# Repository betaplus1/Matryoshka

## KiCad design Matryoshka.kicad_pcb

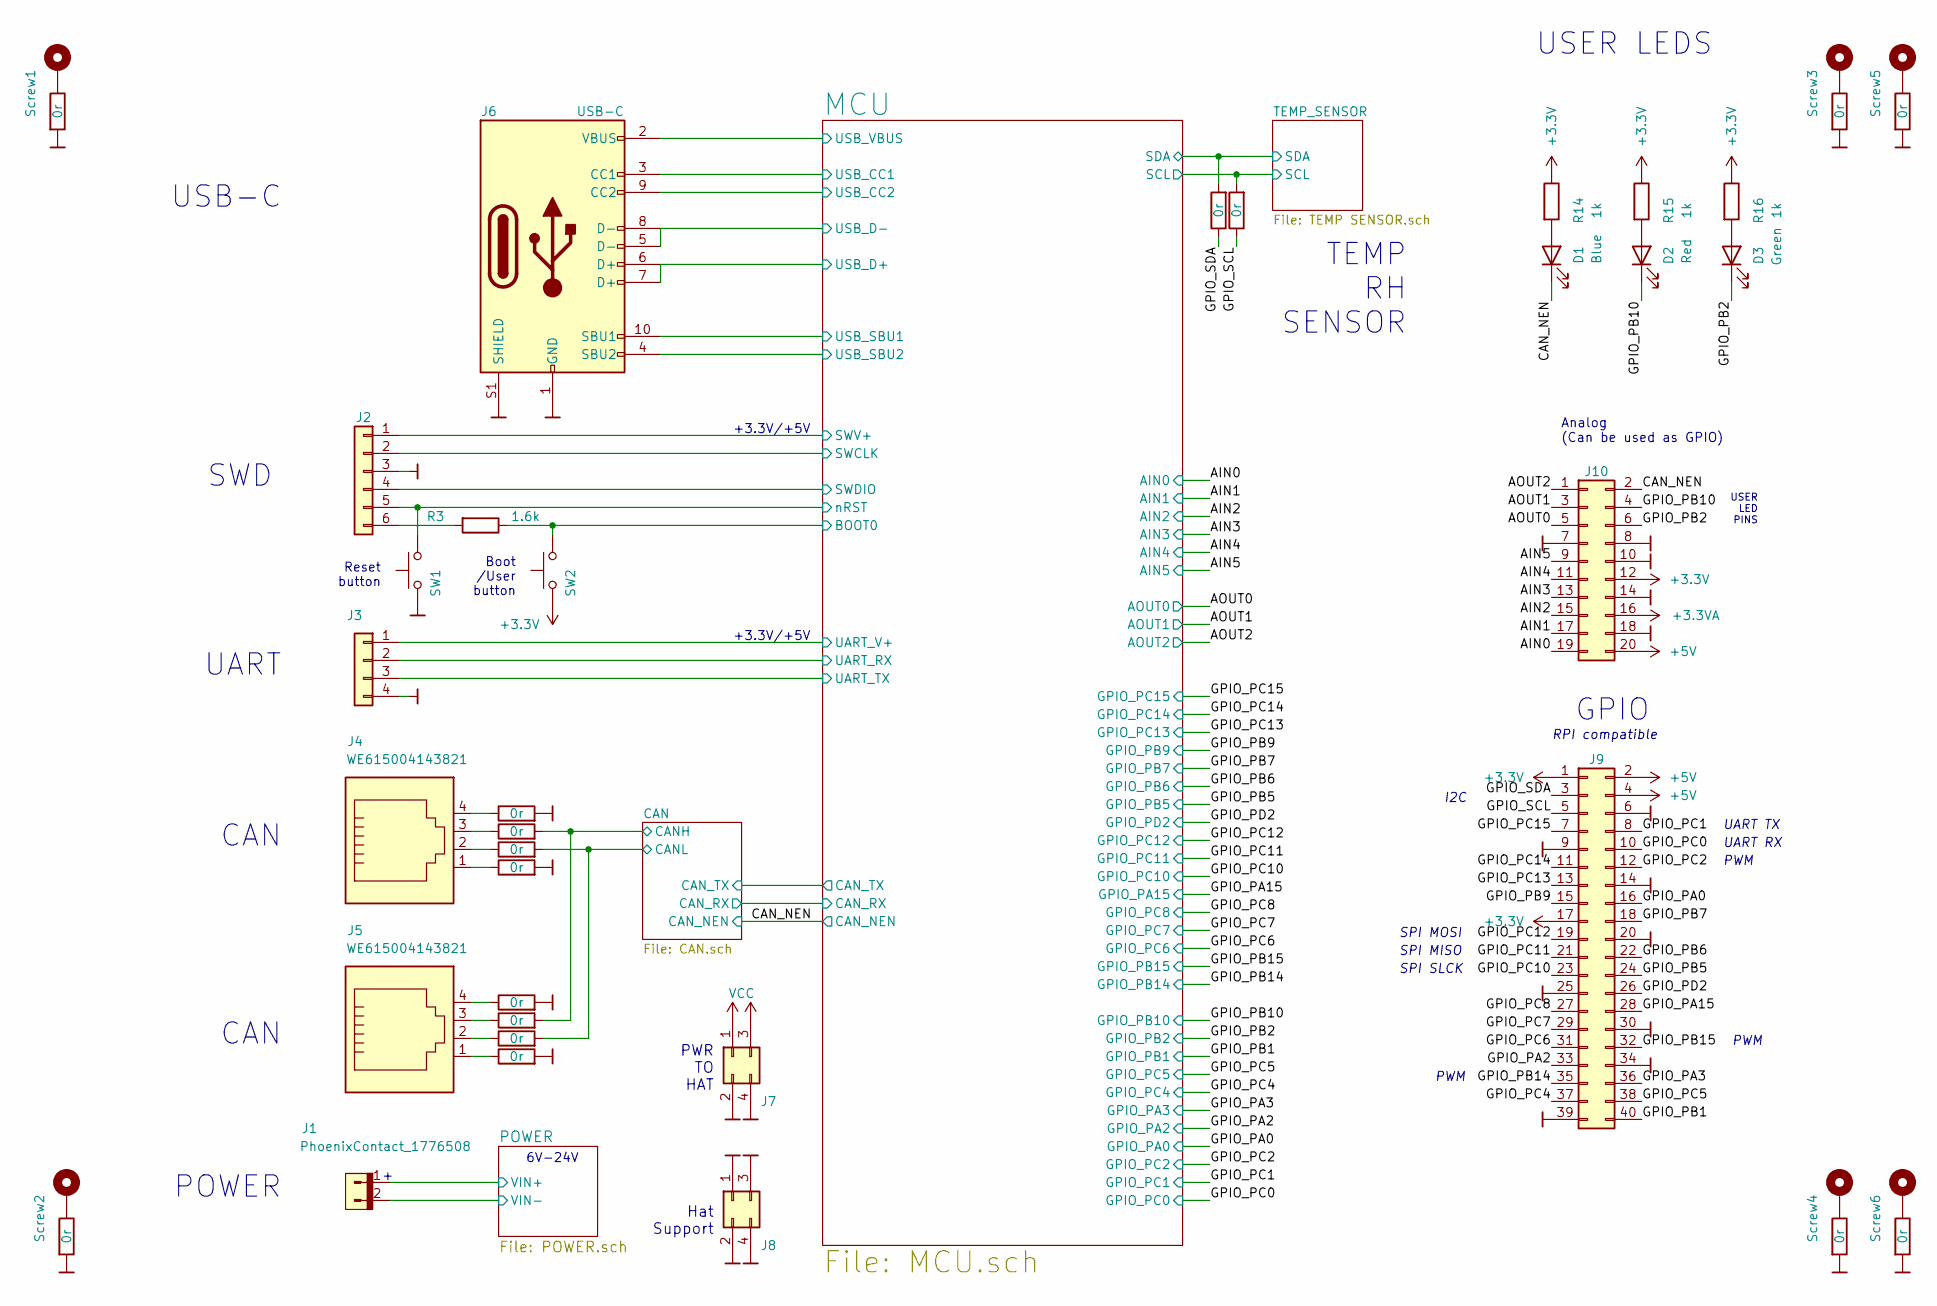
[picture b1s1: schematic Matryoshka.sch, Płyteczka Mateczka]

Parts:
D1: LED_BLUE_ANGLE; WUERTH_155124
D2: LED_RED_ANGLE; WUERTH_155124
D3: LED_GREEN_ANGLE; WUERTH_155124
J1: PhoenixContact_1776508; PhoenixContact_MSTB_2,5_2-GF-5,08_1x02_P5.08mm_Horizontal_T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
J2: Goldpin1x6_right; PinHeader_1x06_P2.54mm_Horizontal
J3: Goldpin1x4_right; PinHeader_1x04_P2.54mm_Horizontal
J4, J5: WE615004143821; WE_615004143821
J6: USB-C; JAE_DX07S016JA1R1500
J7, J8: M20-9980246; PinHeader_2x02_P2.54mm_Vertical
J9: M20-9982046; PinHeader_2x20_P2.54mm_Vertical
J10: M20-9981046; PinHeader_2x10_P2.54mm_Vertical
R1, R2, R4, R5, R6, R7, R8, R9, R10, R11, R12, R13, R17, R18, R19, R20: 0r; R_0603_1608Metric_Pad0.98x0.95mm_HandSolder
R3: 1.6k; R_0603_1608Metric_Pad0.98x0.95mm_HandSolder
R14, R15, R16: 1k; R_0603_1608Metric_Pad0.98x0.95mm_HandSolder
SW1, SW2: Button_Angle; SW_Tactile_SPST_Angled_PTS645Vx83-2LFS
Screw1, Screw2, Screw3, Screw4, Screw5, Screw6: MountingHole_Pad; MountingHole_3.2mm_M3_Pad

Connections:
+3.3VA: J10.16; also elsewhere on the board
+5V: J9.2, J9.4, J10.20; also elsewhere on the board
/AIN0: J10.19; also elsewhere on the board
/AIN1: J10.17; also elsewhere on the board
/AIN2: J10.15; also elsewhere on the board
/AIN3: J10.13; also elsewhere on the board
/AIN4: J10.11; also elsewhere on the board
/AIN5: J10.9; also elsewhere on the board
/AOUT0: J10.5; also elsewhere on the board
/AOUT1: J10.3; also elsewhere on the board
/AOUT2: J10.1; also elsewhere on the board
/CAN/CANH: R5.2, R9.2; also elsewhere on the board
/CAN/CANL: R6.2, R10.2; also elsewhere on the board
/CAN_NEN: D1.C, J10.2; also elsewhere on the board
/GPIO_PA0: J9.16; also elsewhere on the board
/GPIO_PA2: J9.33; also elsewhere on the board
/GPIO_PA3: J9.36; also elsewhere on the board
/GPIO_PA15: J9.28; also elsewhere on the board
/GPIO_PB1: J9.40; also elsewhere on the board
/GPIO_PB2: D3.C, J10.6; also elsewhere on the board
/GPIO_PB5: J9.24; also elsewhere on the board
/GPIO_PB6: J9.22; also elsewhere on the board
/GPIO_PB7: J9.18; also elsewhere on the board
/GPIO_PB9: J9.15; also elsewhere on the board
/GPIO_PB10: D2.C, J10.4; also elsewhere on the board
/GPIO_PB14: J9.35; also elsewhere on the board
/GPIO_PB15: J9.32; also elsewhere on the board
/GPIO_PC0: J9.10; also elsewhere on the board
/GPIO_PC1: J9.8; also elsewhere on the board
/GPIO_PC2: J9.12; also elsewhere on the board
/GPIO_PC4: J9.37; also elsewhere on the board
/GPIO_PC5: J9.38; also elsewhere on the board
/GPIO_PC6: J9.31; also elsewhere on the board
/GPIO_PC7: J9.29; also elsewhere on the board
/GPIO_PC8: J9.27; also elsewhere on the board
/GPIO_PC10: J9.23; also elsewhere on the board
/GPIO_PC11: J9.21; also elsewhere on the board
/GPIO_PC12: J9.19; also elsewhere on the board
/GPIO_PC13: J9.13; also elsewhere on the board
/GPIO_PC14: J9.11; also elsewhere on the board
/GPIO_PC15: J9.7; also elsewhere on the board
/GPIO_PD2: J9.26; also elsewhere on the board
/GPIO_SCL: J9.5, R13.1
/GPIO_SDA: J9.3, R12.1
/MCU/BOOT0: R3.1, SW2.2; also elsewhere on the board
/MCU/SCL: R13.2; also elsewhere on the board
/MCU/SDA: R12.2; also elsewhere on the board
/MCU/SWCLK: J2.2; also elsewhere on the board
/MCU/SWDIO: J2.4; also elsewhere on the board
/MCU/SWV+: J2.1; also elsewhere on the board
/MCU/UART_RX: J3.2; also elsewhere on the board
/MCU/UART_TX: J3.3; also elsewhere on the board
/MCU/UART_V+: J3.1; also elsewhere on the board
/MCU/USB_CC1: J6.3 (CC1); also elsewhere on the board
/MCU/USB_CC2: J6.9 (CC2); also elsewhere on the board
/MCU/USB_D+: J6.6 (D+), J6.7 (D+); also elsewhere on the board
/MCU/USB_D-: J6.5 (D-), J6.8 (D-); also elsewhere on the board
/MCU/USB_VBUS: J6.2 (VBUS), J6.11 (VBUS); also elsewhere on the board
/MCU/nRST: J2.5, SW1.2; also elsewhere on the board
/POWER/VIN+: J1.1; also elsewhere on the board
GND: J1.2, J2.3, J3.4, J6.1 (GND), J6.12 (GND), J6.S1 (SHIELD), J6.S2 (SHIELD), J7.2, J7.4, J8.1, J8.2, J8.3, J8.4, J9.6, J9.9, J9.14, J9.20, J9.25, J9.30, J9.34, J9.39, J10.7, J10.8, J10.10, J10.14, J10.18, R1.2, R2.2, R4.2, R7.2, R8.2, R11.2, R17.2, R18.2, R19.2, R20.2, SW1.1; also elsewhere on the board
unnamed: D1.A, R14.2
unnamed: D2.A, R15.2
unnamed: D3.A, R16.2
unnamed: J2.6, R3.2
unnamed: J4.1, R7.1
unnamed: J4.2, R6.1
unnamed: J4.3, R5.1
unnamed: J4.4, R4.1
unnamed: J5.1, R11.1
unnamed: J5.2, R10.1
unnamed: J5.3, R9.1
unnamed: J5.4, R8.1
unnamed: R1.1, Screw1.1
unnamed: R2.1, Screw2.1
unnamed: R17.1, Screw3.1
unnamed: R18.1, Screw4.1
unnamed: R19.1, Screw5.1
unnamed: R20.1, Screw6.1
VCC: J7.1, J7.3; also elsewhere on the board

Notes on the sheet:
UART
Reset button
CAN
POWER
GPIO
UART TX
PWM
SPI MOSI
SPI MISO
SPI SLCK
UART RX
I2C
RPI compatible
Analog (Can be used as GPIO)
USB-C
USER LEDS
TEMP RH SENSOR
PWM
Boot /User button
SWD
6V-24V
Hat Support
PWR TO HAT
USER LED PINS
+3.3V/+5V

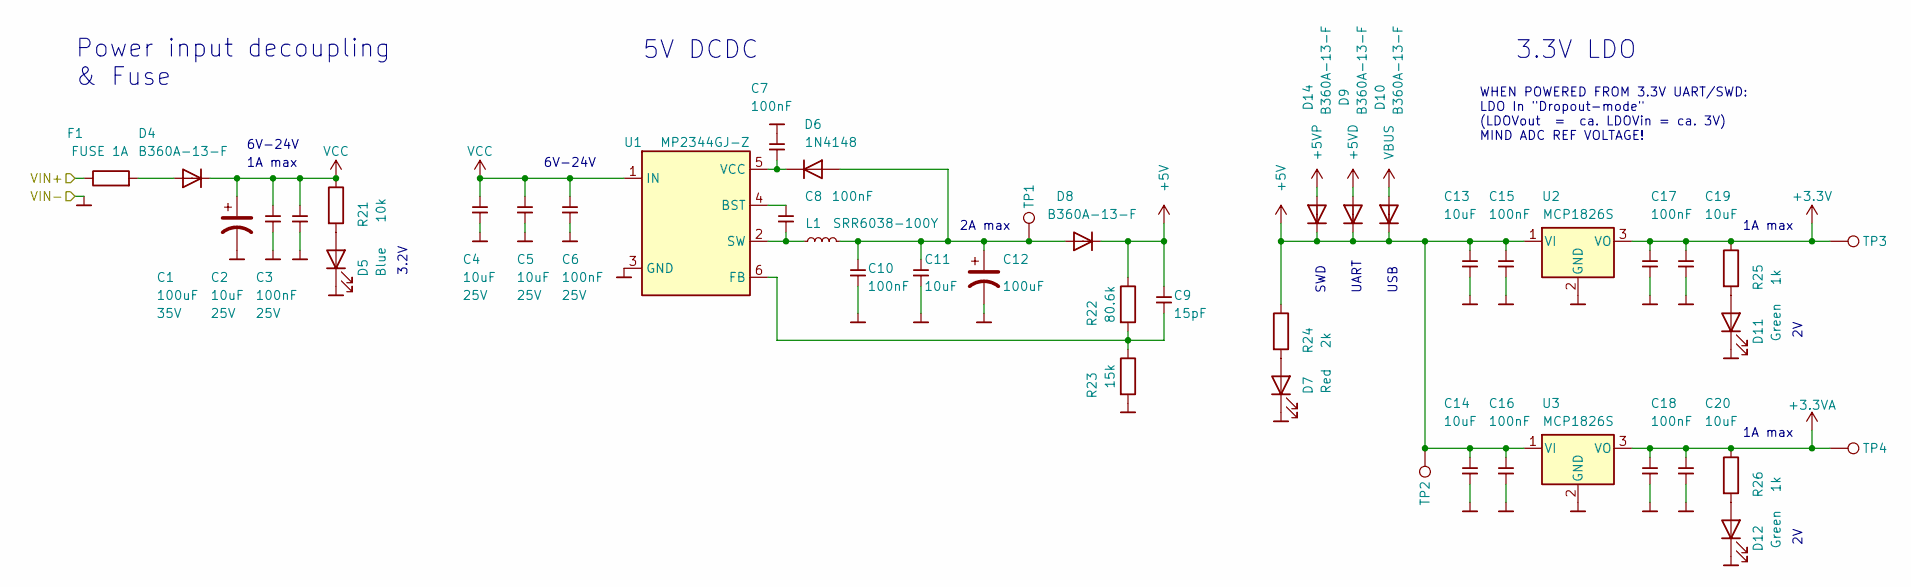
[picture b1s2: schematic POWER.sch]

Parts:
C1: 100uF; CP_Elec_6.3x7.7; Voltage Rating 35V
C2, C4, C5: 10uF; C_0805_2012Metric_Pad1.18x1.45mm_HandSolder; Voltage Rating 25V
C3, C6: 100nF; C_0603_1608Metric_Pad1.08x0.95mm_HandSolder; Voltage Rating 25V
C7, C8, C10, C15, C16, C17, C18: 100nF; C_0603_1608Metric_Pad1.08x0.95mm_HandSolder
C9: 15pF; C_0603_1608Metric_Pad1.08x0.95mm_HandSolder
C11, C13, C14, C19, C20: 10uF; C_0805_2012Metric_Pad1.18x1.45mm_HandSolder
C12: 100uF; CP_EIA-3216-18_Kemet-A_Pad1.58x1.35mm_HandSolder
D4, D8, D9, D10, D14: B360A-13-F; D_SMA_Handsoldering
D5: LED_BLUE_ANGLE; WUERTH_155124
D6: 1N4148; D_SOD-523
D7: LED_RED_ANGLE; WUERTH_155124
D11, D12: LED_GREEN_ANGLE; WUERTH_155124
F1: FUSE 1A; R_0603_1608Metric_Pad0.98x0.95mm_HandSolder
L1: SRR6038-100Y; L_Bourns_SRR6038
R21: 10k; R_0603_1608Metric_Pad0.98x0.95mm_HandSolder
R22: 80.6k; R_0603_1608Metric_Pad0.98x0.95mm_HandSolder
R23: 15k; R_0603_1608Metric_Pad0.98x0.95mm_HandSolder
R24: 2k; R_0603_1608Metric_Pad0.98x0.95mm_HandSolder
R25, R26: 1k; R_0603_1608Metric_Pad0.98x0.95mm_HandSolder
TP1, TP2, TP3, TP4: TestPoint_Pad_D1.5mm
U1: MP2344GJ-Z; TSOT-23-6_HandSoldering
U2, U3: MCP1826S; SOT-223-3_TabPin2

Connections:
+3.3VA: C18.1, C20.1, R26.1, TP4.1, U3.3 (VO); also elsewhere on the board
+5V: C9.1, C13.1, C14.1, C15.1, C16.1, D8.1 (K), D9.1 (K), D10.1 (K), D14.1 (K), R22.1, R24.1, TP2.1, U2.1 (VI), U3.1 (VI); also elsewhere on the board
+5VD: D9.2 (A); also elsewhere on the board
+5VP: D14.2 (A); also elsewhere on the board
/POWER/VIN+: F1.1; also elsewhere on the board
GND: C1.2, C2.2, C3.2, C4.2, C5.2, C6.2, C7.1, C10.2, C11.2, C12.2, C13.2, C14.2, C15.2, C16.2, C17.2, C18.2, C19.2, C20.2, D5.C, D7.C, D11.C, D12.C, R23.2, U1.3 (GND), U2.2 (GND), U3.2 (GND); also elsewhere on the board
unnamed: C7.2, D6.1 (K), U1.5 (VCC)
unnamed: C8.1, U1.4 (BST)
unnamed: C8.2, L1.1, U1.2 (SW)
unnamed: C9.2, R22.2, R23.1, U1.6 (FB)
unnamed: C10.1, C11.1, C12.1, D6.2 (A), D8.2 (A), L1.2, TP1.1
unnamed: D4.2 (A), F1.2
unnamed: D5.A, R21.2
unnamed: D7.A, R24.2
unnamed: D11.A, R25.2
unnamed: D12.A, R26.2
VBUS: D10.2 (A); also elsewhere on the board
VCC: C1.1, C2.1, C3.1, C4.1, C5.1, C6.1, D4.1 (K), R21.1, U1.1 (IN); also elsewhere on the board

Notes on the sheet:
1A max
2A max
3.2V
Power input decoupling & Fuse
5V DCDC
3.3V LDO
USB
UART
SWD
WHEN POWERED FROM 3.3V UART/SWD: LDO In "Dropout-mode" (LDOVout = ca. LDOVin = ca. 3V) MIND ADC REF VOLTAGE!
6V-24V

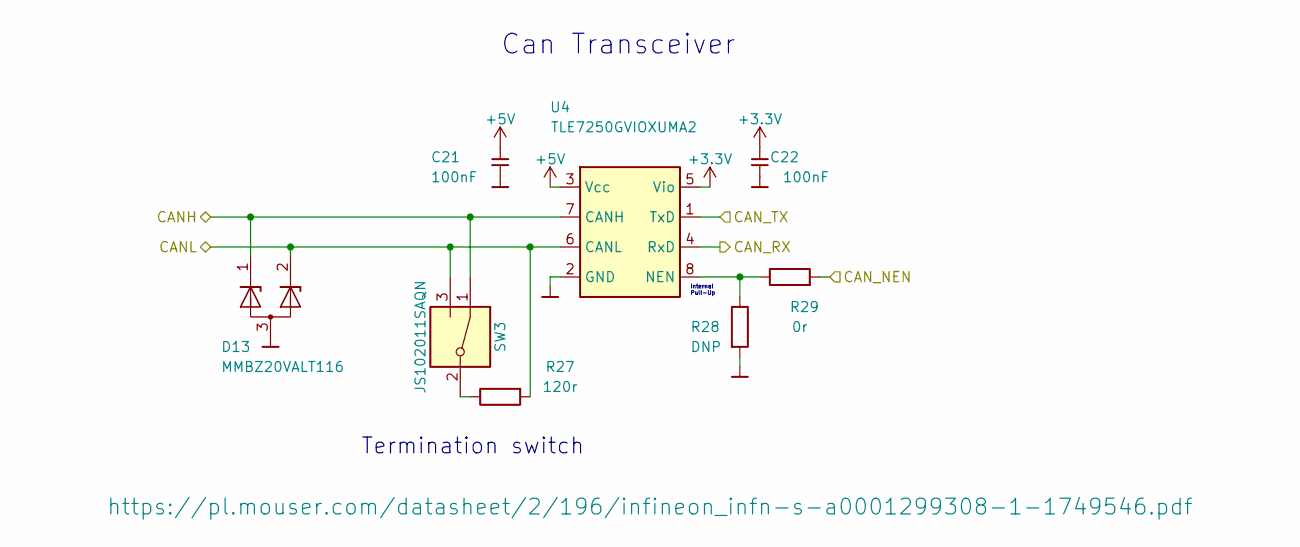
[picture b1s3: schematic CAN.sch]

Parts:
C21, C22: 100nF; C_0603_1608Metric_Pad1.08x0.95mm_HandSolder
D13: MMBZ20VALT116; SOT-23
R27: 120r; R_0603_1608Metric_Pad0.98x0.95mm_HandSolder
R28: DNP; R_0603_1608Metric_Pad0.98x0.95mm_HandSolder
R29: 0r; R_0603_1608Metric_Pad0.98x0.95mm_HandSolder
SW3: JS102011SAQN; SW_SPDT_CK-JS102011SAQN
U4: TLE7250GVIOXUMA2; SO-8_3.9x4.9mm_P1.27mm

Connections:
+5V: C21.1, U4.3 (Vcc); also elsewhere on the board
/CAN/CANH: D13.1 (K), SW3.1, U4.7 (CANH); also elsewhere on the board
/CAN/CANL: D13.2 (K), R27.2, SW3.3, U4.6 (CANL); also elsewhere on the board
/CAN/CAN_RX: U4.4 (RxD); also elsewhere on the board
/CAN/CAN_TX: U4.1 (TxD); also elsewhere on the board
/CAN_NEN: R29.2; also elsewhere on the board
GND: C21.2, C22.2, D13.3 (A), R28.2, U4.2 (GND); also elsewhere on the board
unnamed: R27.1, SW3.2
unnamed: R28.1, R29.1, U4.8 (NEN)

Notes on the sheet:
Internal Pull-Up
Termination switch
Can Transceiver

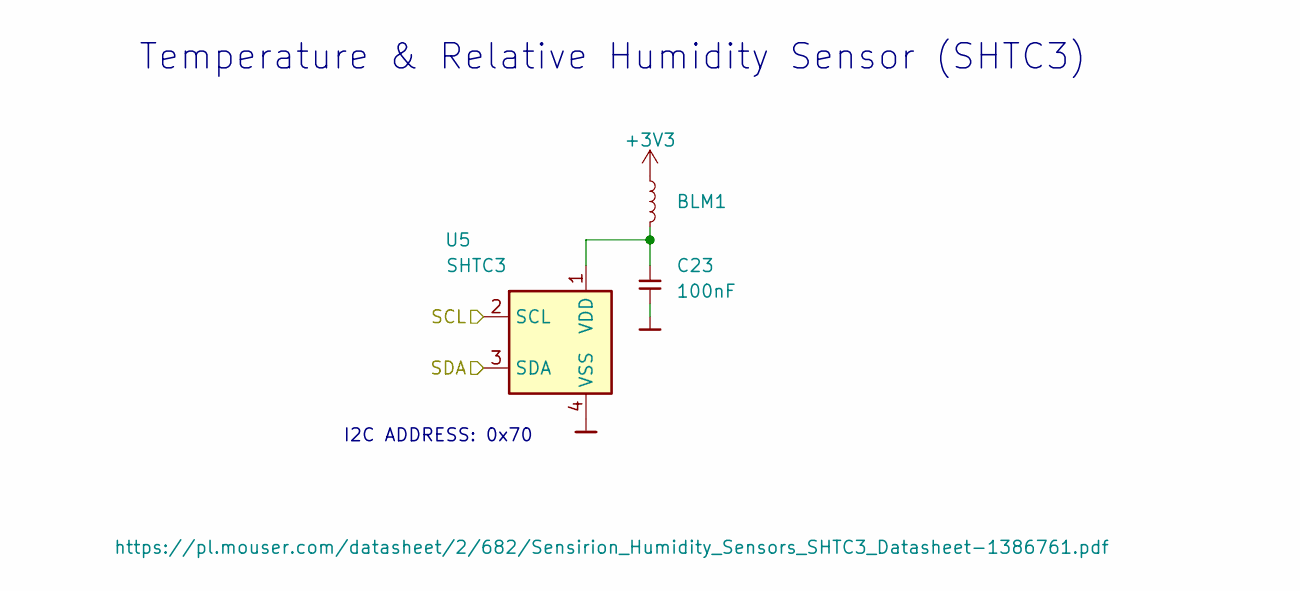
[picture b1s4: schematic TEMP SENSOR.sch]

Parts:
BLM1: BLM18KG102SN1D; L_0603_1608Metric_Pad1.05x0.95mm_HandSolder
C23: 100nF; C_0603_1608Metric_Pad1.08x0.95mm_HandSolder
U5: SHTC3; Sensirion_DFN-4-1EP_2x2mm_P1mm_EP0.7x1.6mm

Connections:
/MCU/SCL: U5.2 (SCL); also elsewhere on the board
/MCU/SDA: U5.3 (SDA); also elsewhere on the board
GND: C23.2, U5.4 (VSS); also elsewhere on the board
unnamed: BLM1.2, C23.1, U5.1 (VDD)

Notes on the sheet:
I2C ADDRESS: 0x70
Temperature & Relative Humidity Sensor (SHTC3)

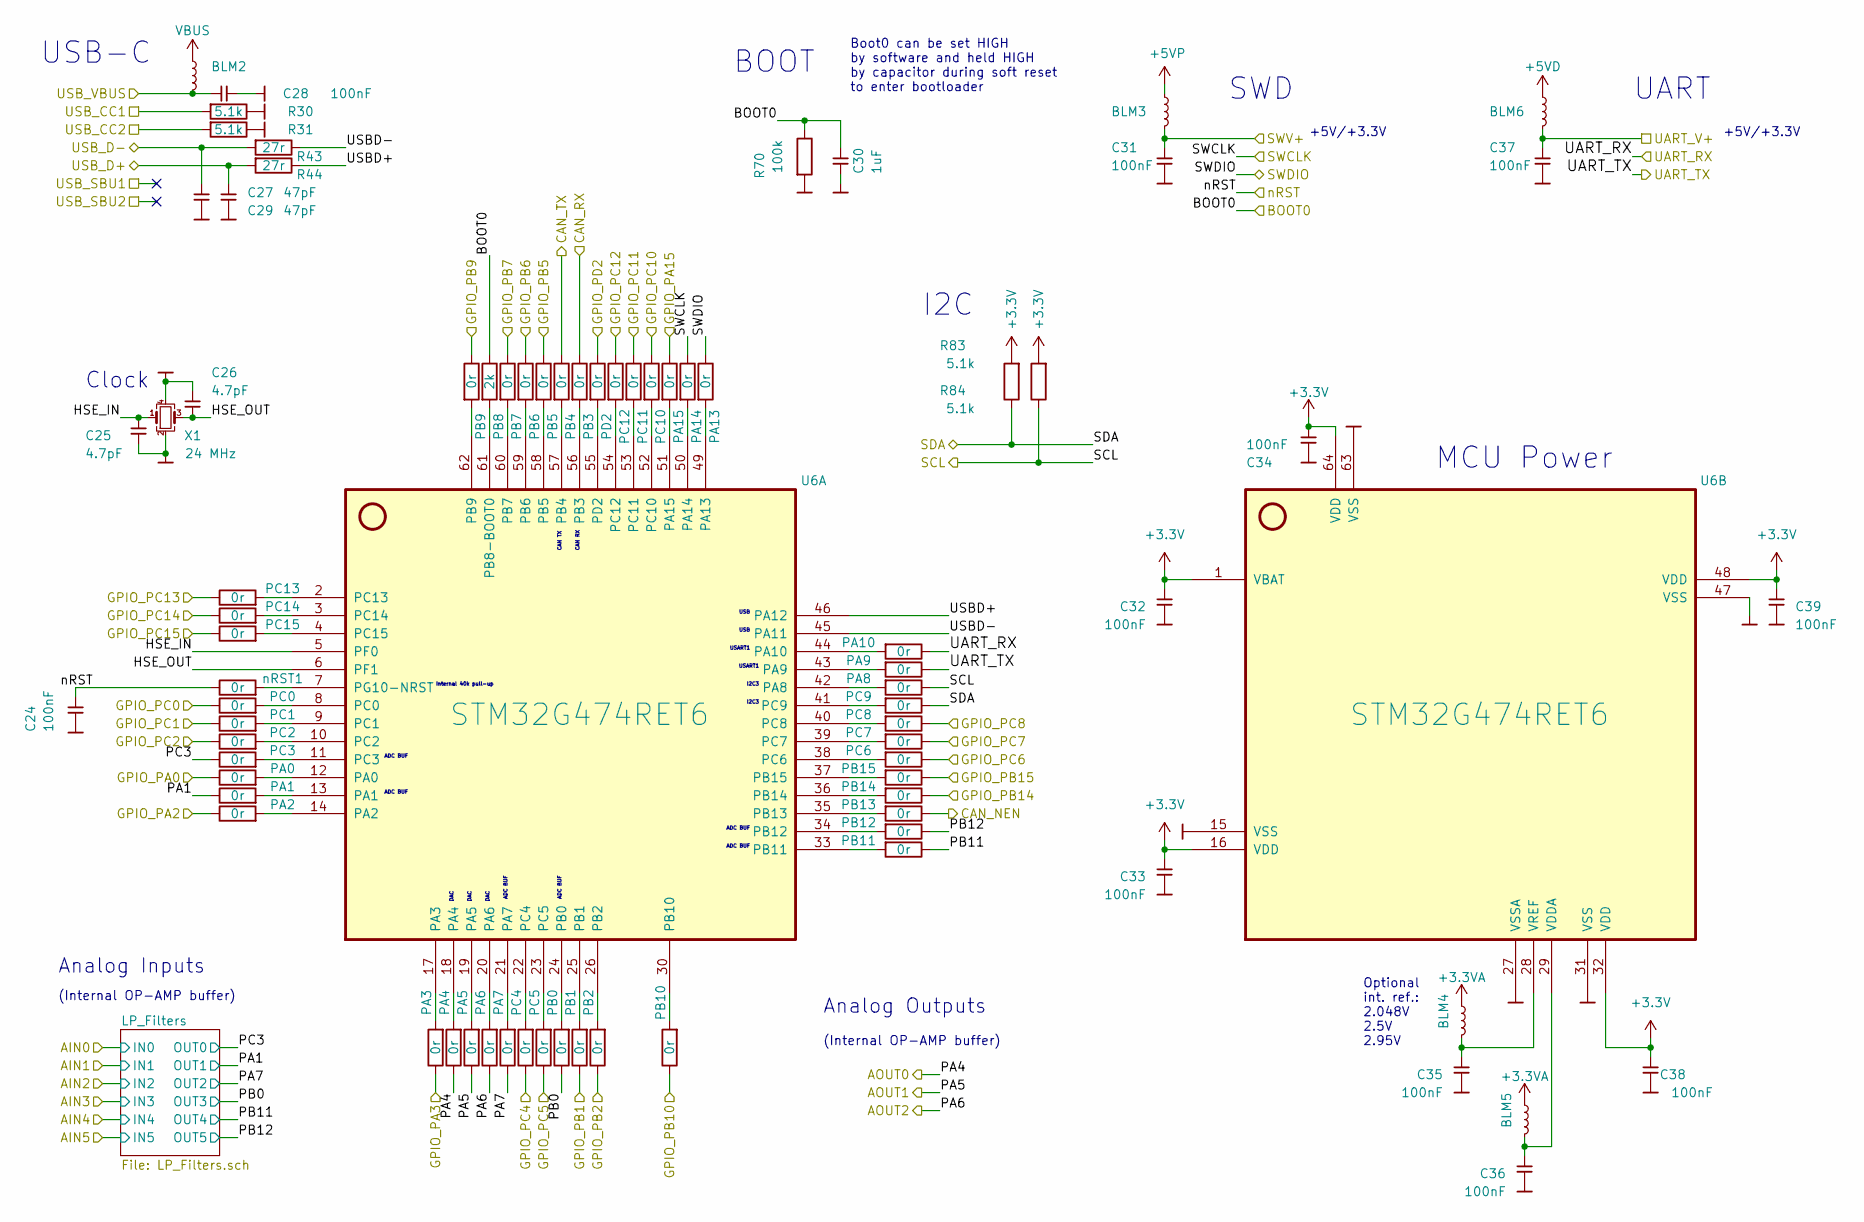
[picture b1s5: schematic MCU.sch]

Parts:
BLM2, BLM3, BLM4, BLM5, BLM6: BLM18KG102SN1D; L_0603_1608Metric_Pad1.05x0.95mm_HandSolder
C24, C28, C31, C32, C33, C34, C35, C36, C37, C38, C39: 100nF; C_0603_1608Metric_Pad1.08x0.95mm_HandSolder
C25, C26: 4.7pF; C_0603_1608Metric_Pad1.08x0.95mm_HandSolder
C27, C29: 47pF; C_0603_1608Metric_Pad1.08x0.95mm_HandSolder
C30: 1uF; C_0603_1608Metric_Pad1.08x0.95mm_HandSolder
PA0, PA1, PA2, PA3, PA4, PA5, PA6, PA7, PA8, PA9, PA10, PA13, PA14, PA15: 0r; R_0603_1608Metric_Pad0.98x0.95mm_HandSolder
PB0, PB1, PB2, PB3, PB4, PB5, PB6, PB7, PB9, PB10, PB11, PB12, PB13, PB14, PB15: 0r; R_0603_1608Metric_Pad0.98x0.95mm_HandSolder
PB8: 2k; R_0603_1608Metric_Pad0.98x0.95mm_HandSolder
PC0, PC1, PC2, PC3, PC4, PC5, PC6, PC7, PC8, PC9, PC10, PC11, PC12, PC13, PC14, PC15: 0r; R_0603_1608Metric_Pad0.98x0.95mm_HandSolder
PD2: 0r; R_0603_1608Metric_Pad0.98x0.95mm_HandSolder
R30, R31, R83, R84: 5.1k; R_0603_1608Metric_Pad0.98x0.95mm_HandSolder
R43, R44: 27r; R_0603_1608Metric_Pad0.98x0.95mm_HandSolder
R70: 100k; R_0603_1608Metric_Pad0.98x0.95mm_HandSolder
U6: STM32G474RET6; LQFP-64_10x10mm_P0.5mm
X1: XRCGB24M000F3M00R0; Crystal_SMD_2016-4Pin_2.0x1.6mm
nRST1: 0r; R_0603_1608Metric_Pad0.98x0.95mm_HandSolder

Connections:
+3.3VA: BLM4.1, BLM5.1; also elsewhere on the board
+5VD: BLM6.2; also elsewhere on the board
+5VP: BLM3.2; also elsewhere on the board
/AOUT0: PA4.1; also elsewhere on the board
/AOUT1: PA5.1; also elsewhere on the board
/AOUT2: PA6.1; also elsewhere on the board
/CAN/CAN_RX: PB3.1; also elsewhere on the board
/CAN/CAN_TX: PB4.1; also elsewhere on the board
/CAN_NEN: PB13.1; also elsewhere on the board
/GPIO_PA0: PA0.1; also elsewhere on the board
/GPIO_PA2: PA2.1; also elsewhere on the board
/GPIO_PA3: PA3.1; also elsewhere on the board
/GPIO_PA15: PA15.1; also elsewhere on the board
/GPIO_PB1: PB1.1; also elsewhere on the board
/GPIO_PB2: PB2.1; also elsewhere on the board
/GPIO_PB5: PB5.1; also elsewhere on the board
/GPIO_PB6: PB6.1; also elsewhere on the board
/GPIO_PB7: PB7.1; also elsewhere on the board
/GPIO_PB9: PB9.1; also elsewhere on the board
/GPIO_PB10: PB10.1; also elsewhere on the board
/GPIO_PB14: PB14.1; also elsewhere on the board
/GPIO_PB15: PB15.1; also elsewhere on the board
/GPIO_PC0: PC0.1; also elsewhere on the board
/GPIO_PC1: PC1.1; also elsewhere on the board
/GPIO_PC2: PC2.1; also elsewhere on the board
/GPIO_PC4: PC4.1; also elsewhere on the board
/GPIO_PC5: PC5.1; also elsewhere on the board
/GPIO_PC6: PC6.1; also elsewhere on the board
/GPIO_PC7: PC7.1; also elsewhere on the board
/GPIO_PC8: PC8.1; also elsewhere on the board
/GPIO_PC10: PC10.1; also elsewhere on the board
/GPIO_PC11: PC11.1; also elsewhere on the board
/GPIO_PC12: PC12.1; also elsewhere on the board
/GPIO_PC13: PC13.1; also elsewhere on the board
/GPIO_PC14: PC14.1; also elsewhere on the board
/GPIO_PC15: PC15.1; also elsewhere on the board
/GPIO_PD2: PD2.1; also elsewhere on the board
/MCU/BOOT0: C30.1, PB8.1, R70.1; also elsewhere on the board
/MCU/HSE_IN: C25.1, U6.5 (PF0), X1.1
/MCU/HSE_OUT: C26.2, U6.6 (PF1), X1.3
/MCU/PA1: PA1.1; also elsewhere on the board
/MCU/PA7: PA7.1; also elsewhere on the board
/MCU/PB0: PB0.1; also elsewhere on the board
/MCU/PB11: PB11.1; also elsewhere on the board
/MCU/PB12: PB12.1; also elsewhere on the board
/MCU/PC3: PC3.1; also elsewhere on the board
/MCU/SCL: PA8.1, R84.1; also elsewhere on the board
/MCU/SDA: PC9.1, R83.1; also elsewhere on the board
/MCU/SWCLK: PA14.1; also elsewhere on the board
/MCU/SWDIO: PA13.1; also elsewhere on the board
/MCU/SWV+: BLM3.1, C31.1; also elsewhere on the board
/MCU/UART_RX: PA10.1; also elsewhere on the board
/MCU/UART_TX: PA9.1; also elsewhere on the board
/MCU/UART_V+: BLM6.1, C37.1; also elsewhere on the board
/MCU/USBD+: R44.1, U6.46 (PA12)
/MCU/USBD-: R43.1, U6.45 (PA11)
/MCU/USB_CC1: R30.2; also elsewhere on the board
/MCU/USB_CC2: R31.2; also elsewhere on the board
/MCU/USB_D+: C29.1, R44.2; also elsewhere on the board
/MCU/USB_D-: C27.1, R43.2; also elsewhere on the board
/MCU/USB_VBUS: BLM2.2, C28.1; also elsewhere on the board
/MCU/nRST: C24.1, nRST1.1; also elsewhere on the board
GND: C24.2, C25.2, C26.1, C27.2, C28.2, C29.2, C30.2, C31.2, C32.2, C33.2, C34.2, C35.2, C36.2, C37.2, C38.2, C39.2, R30.1, R31.1, R70.2, U6.15 (VSS), U6.27 (VSSA), U6.31 (VSS), U6.47 (VSS), U6.63 (VSS), X1.2, X1.4; also elsewhere on the board
unnamed: BLM4.2, C35.1, U6.28 (VREF)
unnamed: BLM5.2, C36.1, U6.29 (VDDA)
unnamed: PA0.2, U6.12 (PA0)
unnamed: PA1.2, U6.13 (PA1)
unnamed: PA2.2, U6.14 (PA2)
unnamed: PA3.2, U6.17 (PA3)
unnamed: PA4.2, U6.18 (PA4)
unnamed: PA5.2, U6.19 (PA5)
unnamed: PA6.2, U6.20 (PA6)
unnamed: PA7.2, U6.21 (PA7)
unnamed: PA8.2, U6.42 (PA8)
unnamed: PA9.2, U6.43 (PA9)
unnamed: PA10.2, U6.44 (PA10)
unnamed: PA13.2, U6.49 (PA13)
unnamed: PA14.2, U6.50 (PA14)
unnamed: PA15.2, U6.51 (PA15)
unnamed: PB0.2, U6.24 (PB0)
unnamed: PB1.2, U6.25 (PB1)
unnamed: PB2.2, U6.26 (PB2)
unnamed: PB3.2, U6.56 (PB3)
unnamed: PB4.2, U6.57 (PB4)
unnamed: PB5.2, U6.58 (PB5)
unnamed: PB6.2, U6.59 (PB6)
unnamed: PB7.2, U6.60 (PB7)
unnamed: PB8.2, U6.61 (PB8-BOOT0)
unnamed: PB9.2, U6.62 (PB9)
unnamed: PB10.2, U6.30 (PB10)
unnamed: PB11.2, U6.33 (PB11)
unnamed: PB12.2, U6.34 (PB12)
unnamed: PB13.2, U6.35 (PB13)
unnamed: PB14.2, U6.36 (PB14)
unnamed: PB15.2, U6.37 (PB15)
unnamed: PC0.2, U6.8 (PC0)
unnamed: PC1.2, U6.9 (PC1)
unnamed: PC2.2, U6.10 (PC2)
unnamed: PC3.2, U6.11 (PC3)
unnamed: PC4.2, U6.22 (PC4)
unnamed: PC5.2, U6.23 (PC5)
unnamed: PC6.2, U6.38 (PC6)
unnamed: PC7.2, U6.39 (PC7)
unnamed: PC8.2, U6.40 (PC8)
unnamed: PC9.2, U6.41 (PC9)
unnamed: PC10.2, U6.52 (PC10)
unnamed: PC11.2, U6.53 (PC11)
unnamed: PC12.2, U6.54 (PC12)
unnamed: PC13.2, U6.2 (PC13)
unnamed: PC14.2, U6.3 (PC14)
unnamed: PC15.2, U6.4 (PC15)
unnamed: PD2.2, U6.55 (PD2)
unnamed: U6.7 (PG10-NRST), nRST1.2
VBUS: BLM2.1; also elsewhere on the board

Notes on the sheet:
Internal 40k pull-up
Optional int. ref.: 2.048V 2.5V 2.95V
USB-C
I2C
UART
Analog Inputs
(Internal OP-AMP buffer)
Analog Outputs
DAC
ADC BUF
I2C3
USART1
USB
Clock
CAN TX
CAN RX
MCU Power
Boot0 can be set HIGH by software and held HIGH by capacitor during soft reset to enter bootloader
BOOT
SWD
+5V/+3.3V

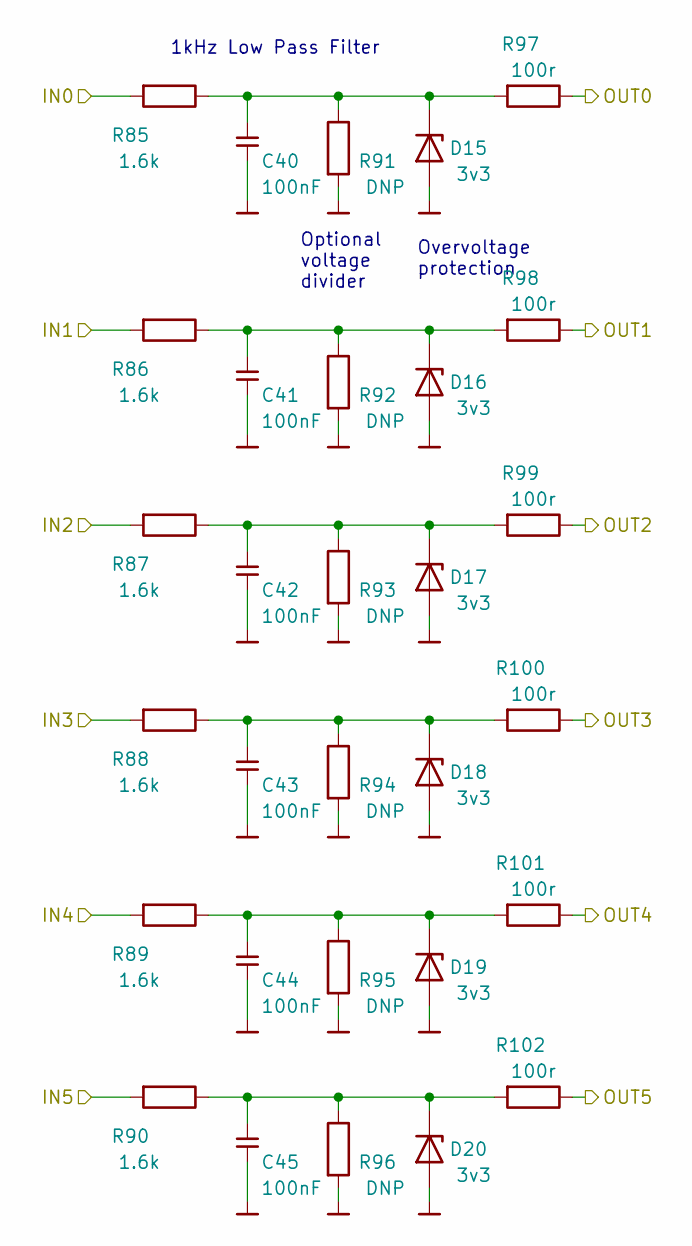
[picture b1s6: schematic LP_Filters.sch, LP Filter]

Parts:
C40, C41, C42, C43, C44, C45: 100nF; C_0603_1608Metric_Pad1.08x0.95mm_HandSolder
D15, D16, D17, D18, D19, D20: MM3Z3V3T1G; D_SOD-323; Voltage 3v3
R85, R86, R87, R88, R89, R90: 1.6k; R_0603_1608Metric_Pad0.98x0.95mm_HandSolder
R91, R92, R93, R94, R95, R96: DNP; R_0603_1608Metric_Pad0.98x0.95mm_HandSolder
R97, R98, R99, R100, R101, R102: 100r; R_0603_1608Metric_Pad0.98x0.95mm_HandSolder

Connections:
/AIN0: R85.2; also elsewhere on the board
/AIN1: R86.2; also elsewhere on the board
/AIN2: R87.2; also elsewhere on the board
/AIN3: R88.2; also elsewhere on the board
/AIN4: R89.2; also elsewhere on the board
/AIN5: R90.2; also elsewhere on the board
/MCU/PA1: R98.1; also elsewhere on the board
/MCU/PA7: R99.1; also elsewhere on the board
/MCU/PB0: R100.1; also elsewhere on the board
/MCU/PB11: R101.1; also elsewhere on the board
/MCU/PB12: R102.1; also elsewhere on the board
/MCU/PC3: R97.1; also elsewhere on the board
GND: C40.2, C41.2, C42.2, C43.2, C44.2, C45.2, D15.2 (A), D16.2 (A), D17.2 (A), D18.2 (A), D19.2 (A), D20.2 (A), R91.2, R92.2, R93.2, R94.2, R95.2, R96.2; also elsewhere on the board
unnamed: C40.1, D15.1 (K), R85.1, R91.1, R97.2
unnamed: C41.1, D16.1 (K), R86.1, R92.1, R98.2
unnamed: C42.1, D17.1 (K), R87.1, R93.1, R99.2
unnamed: C43.1, D18.1 (K), R88.1, R94.1, R100.2
unnamed: C44.1, D19.1 (K), R89.1, R95.1, R101.2
unnamed: C45.1, D20.1 (K), R90.1, R96.1, R102.2

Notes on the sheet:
1kHz Low Pass Filter
Overvoltage protection
Optional voltage divider

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
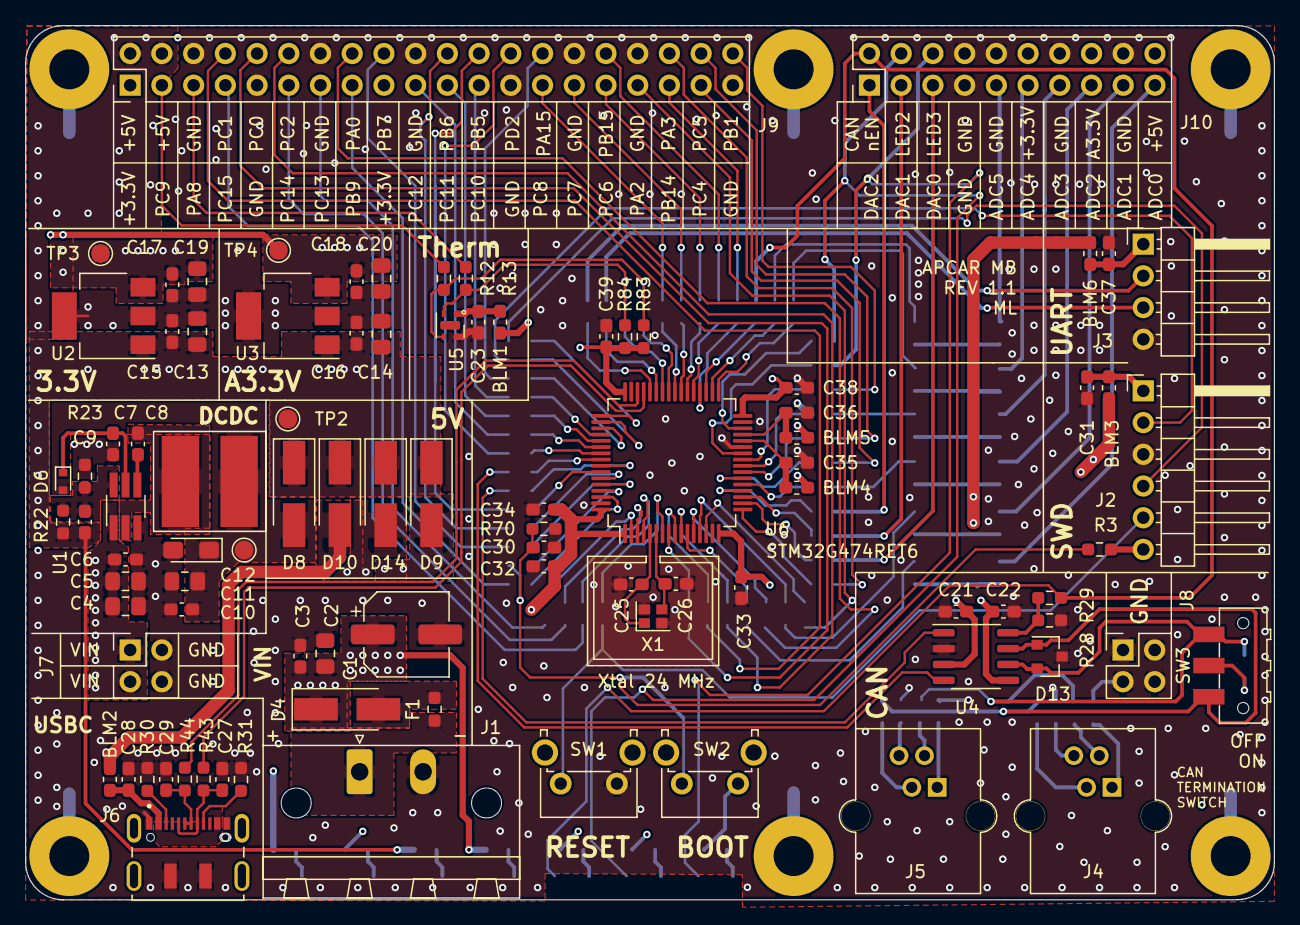
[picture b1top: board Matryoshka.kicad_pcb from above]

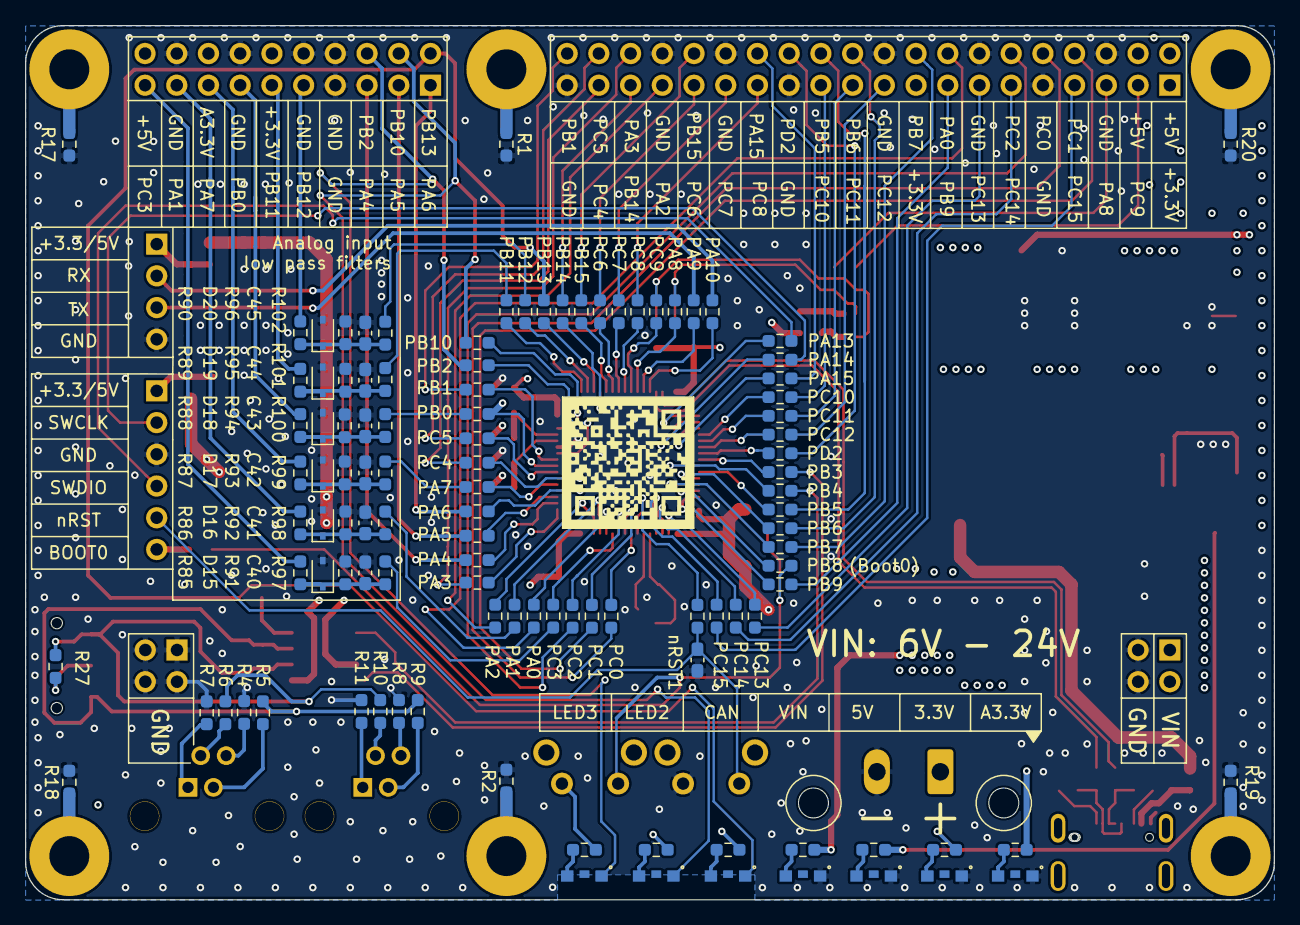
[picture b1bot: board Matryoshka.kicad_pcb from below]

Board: 4 copper layers, 100.0 x 70.0 mm, 205 parts (108 on the bottom side), 165 nets.

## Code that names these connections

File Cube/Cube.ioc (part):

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Mcu.Name=STM32G474R(B-C-E)Tx
Mcu.Package=LQFP64
Mcu.UserName=STM32G474RBTx
PA1.Mode=Follower_Internally_Connected
PA1.Signal=OPAMP1_VINP
PA10.Mode=Asynchronous
PA10.Signal=USART1_RX
PA11.Mode=Device
PA11.Signal=USB_DM
PA12.Mode=Device
PA12.Signal=USB_DP
PA13.Mode=Serial_Wire
PA13.Signal=SYS_JTMS-SWDIO
PA14.Mode=Serial_Wire
PA14.Signal=SYS_JTCK-SWCLK
PA15.Signal=S_TIM2_CH1
PA4.Signal=COMP_DAC11_group
PA5.Signal=COMP_DAC12_group
PA6.Signal=COMP_DAC21_group
PA7.Mode=Follower_Internally_Connected
PA7.Signal=OPAMP2_VINP
PA8.Mode=I2C
PA8.Signal=I2C3_SCL
PA9.Mode=Asynchronous
PA9.Signal=USART1_TX
PB0.Mode=Follower_Internally_Connected
PB0.Signal=OPAMP3_VINP
PB10.GPIOParameters=GPIO_Label
PB10.GPIO_Label=USER LED2
PB10.Signal=GPIO_Output
PB11.Mode=Follower_Internally_Connected
PB11.Signal=OPAMP4_VINP
PB12.Mode=Follower_Internally_Connected
PB12.Signal=OPAMP6_VINP
PB13.GPIOParameters=GPIO_Label
PB13.GPIO_Label=USER LED 3
PB13.Signal=GPIO_Output
PB14.Signal=S_TIM15_CH1
PB2.GPIOParameters=GPIO_Label
PB2.GPIO_Label=USER LED1
PB2.Signal=GPIO_Output
PB3.Mode=FDCANMaster
PB3.Signal=FDCAN3_RX
PB4.Mode=FDCANMaster
PB4.Signal=FDCAN3_TX
PC0.Signal=LPUART1_RX
PC1.Signal=LPUART1_TX
PC10.Signal=SPI3_SCK
PC11.Signal=SPI3_MISO
PC12.Signal=SPI3_MOSI
PC2.Signal=S_TIM1_CH3
PC3.Mode=Follower_Internally_Connected
PC3.Signal=OPAMP5_VINP
PC9.Mode=I2C
PC9.Signal=I2C3_SDA
PF0-OSC_IN.Mode=HSE-External-Oscillator
PF0-OSC_IN.Signal=RCC_OSC_IN
PF1-OSC_OUT.Mode=HSE-External-Oscillator
PF1-OSC_OUT.Signal=RCC_OSC_OUT
PG10-NRST.GPIOParameters=GPIO_Label
PG10-NRST.GPIO_Label=NRST
PG10-NRST.Signal=GPXTI10
RCC.HSE_VALUE=8000000
RCC.SYSCLKFreq_VALUE=16000000
board=custom
